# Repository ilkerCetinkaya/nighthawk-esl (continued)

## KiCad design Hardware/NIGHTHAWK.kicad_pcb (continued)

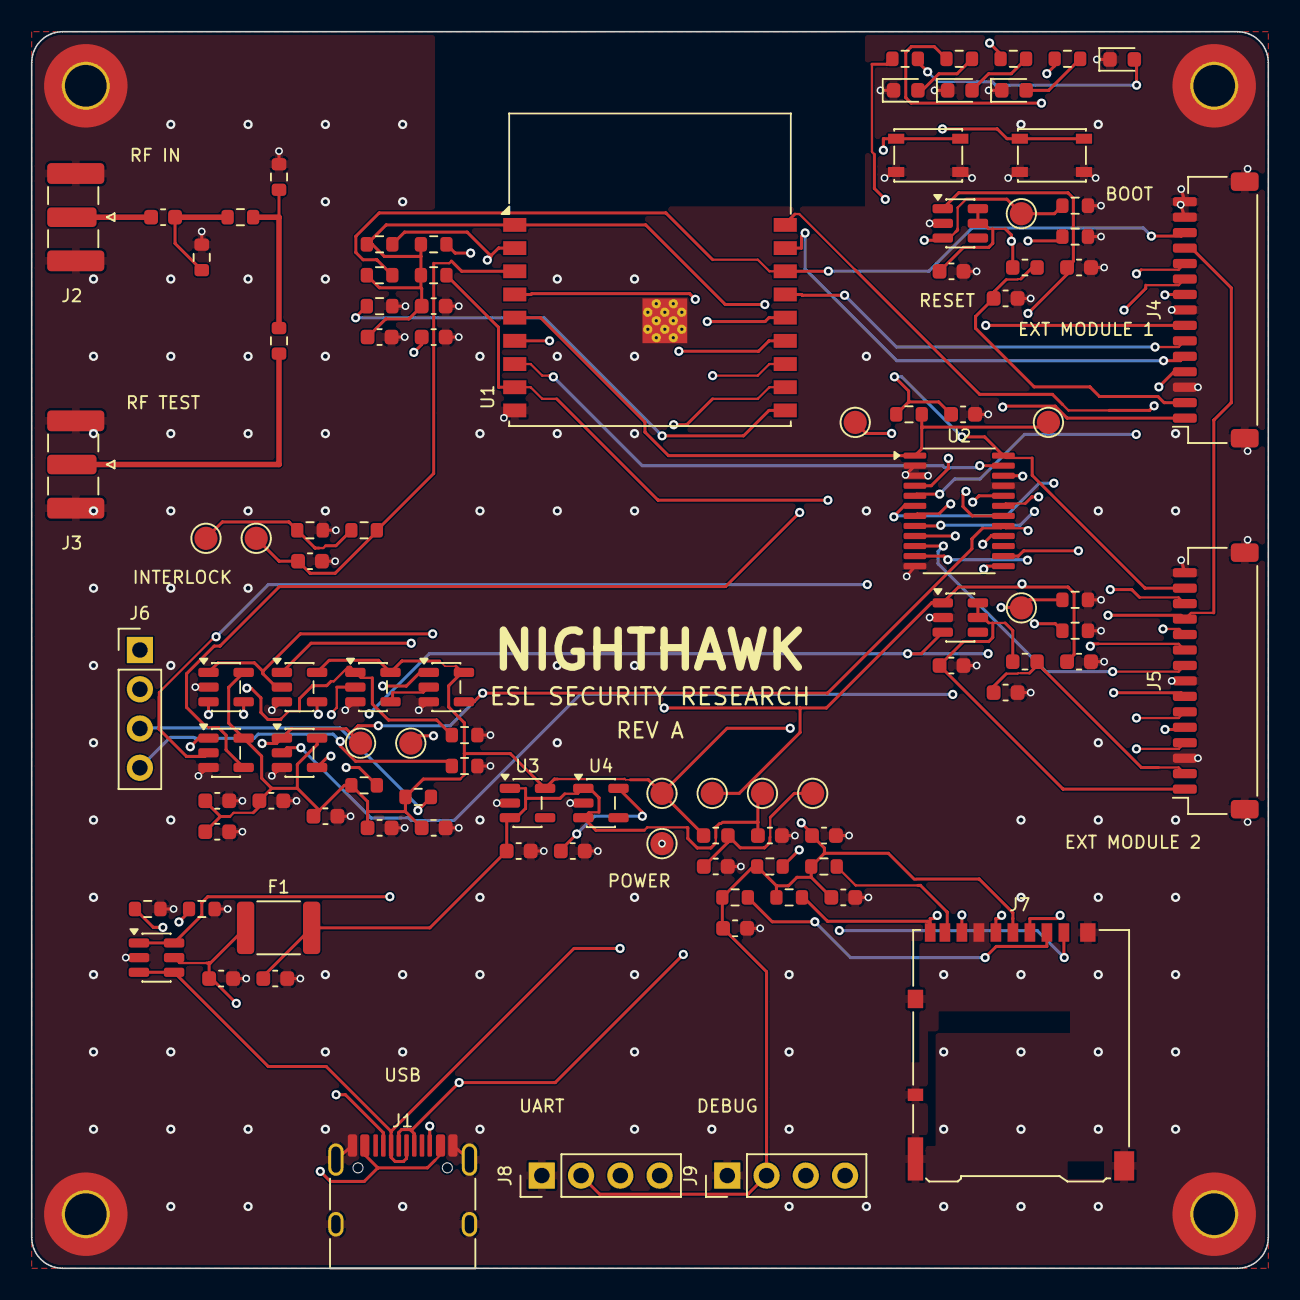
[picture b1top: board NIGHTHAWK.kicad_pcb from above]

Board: 4 copper layers, 80.0 x 80.0 mm, 106 parts (0 on the bottom side), 63 nets.

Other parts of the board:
H1, H2, H3, H4: M2.5; MountingHole_2.7mm_M2.5_Pad_TopBottom

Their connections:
GND: H1.1, H2.1, H3.1, H4.1; also elsewhere on the board

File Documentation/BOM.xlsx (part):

Reference | Quantity | Value | Description | Manufacturer | Manufacturer Part Number | LCSC Part Number | Footprint | Package | Unit Price (USD) | Total Price (USD) | Datasheet URL | Stock | Alternative | Verification Status | Assembly Status
U1 | 1 | ESP32-C3-WROOM-02-N4 | ESP32-C3 module, 4 MB flash, PCB antenna | Espressif | ESP32-C3-WROOM-02-N4 | C2934560 | RF_Module:ESP32-C3-WROOM-02 | ESP32-C3-WROOM-02 | 3.3224 | 3.3224 | https://www.lcsc.com/product-detail/C2934560.html | 13503 | C2926676 (ESP32-C3-WROOM-02U-N4, external antenna) | Verified on LCSC page (read in browser) 2026-11-07 (price at 1+ qty tier) | JLCPCB SMT
C1,C6,C7,C8,C9,C10,C11,C16,C19,C26 | 10 | 10u | 10 uF 10 V 0603 ceramic | Samsung Electro-Mechanics | CL10A106KP8NNNC | C19702 | Capacitor_SMD:C_0603_1608Metric | C_0603_1608Metric | 0.0205 | 0.205 | https://www.lcsc.com/product-detail/C19702.html | 1675120 |  | Verified on LCSC page (read in browser) 2026-11-07 (price at 20+ qty tier) | JLCPCB SMT
C2,C4,C5,C13,C20,C21,C22,C23,C24,C25,C27 | 11 | 100n | 100 nF 16 V X7R 0603 | YAGEO | CC0603KRX7R7BB104 | C108079 | Capacitor_SMD:C_0603_1608Metric | C_0603_1608Metric | 0.0121 | 0.1331 | https://www.lcsc.com/product-detail/C108079.html | 1165800 |  | Verified on LCSC page (read in browser) 2026-11-07 (price at 50+ qty tier) | JLCPCB SMT
R1,R4,R5,R6,R13,R15,R16,R17,R18,R19,R20,R23,R24,R25,R26 | 15 | 10k | 10 kohm 1% 0603 resistor | UNI-ROYAL | 0603WAF1002T5E | C25804 | Resistor_SMD:R_0603_1608Metric | R_0603_1608Metric | 0.0024 | 0.036 | https://www.lcsc.com/product-detail/C25804.html | 3592800 |  | Verified on LCSC page (read in browser) 2026-11-07 (price at 100+ qty tier) | JLCPCB SMT
C3,C14,C15,C17,C18 | 5 | 1u | 1 uF 0603 ceramic | Samsung Electro-Mechanics | CL10A105KB8NNNC | C15849 | Capacitor_SMD:C_0603_1608Metric | C_0603_1608Metric | 0.011 | 0.05499999999999999 | https://www.lcsc.com/product-detail/C15849.html | 1524300 |  | Verified on LCSC page (read in browser) 2026-11-07 (price at 50+ qty tier) | JLCPCB SMT
R2,R3 | 2 | 4.7k | 4.7 kohm 1% 0603 resistor | UNI-ROYAL | 0603WAF4701T5E | C23162 | Resistor_SMD:R_0603_1608Metric | R_0603_1608Metric | 0.0028 | 0.0056 | https://www.lcsc.com/product-detail/C23162.html | 3969400 |  | Verified on LCSC page (read in browser) 2026-11-07 (price at 100+ qty tier) | JLCPCB SMT
U2 | 1 | TCA9555PWR | 16-bit I2C GPIO expander TSSOP-24 | Texas Instruments | TCA9555PWR | C465732 | Package_SO:TSSOP-24_4.4x7.8mm_P0.65mm | TSSOP-24_4.4x7.8mm_P0.65mm | 0.7076 | 0.7076 | https://www.lcsc.com/product-detail/C465732.html | 27264 |  | Verified on LCSC page (read in browser) 2026-11-07 (price at 1+ qty tier) | JLCPCB SMT
J1 | 1 | TYPE-C-31-M-12 | USB-C receptacle 16-pin SMT | Korean Hroparts Elec | TYPE-C-31-M-12 | C165948 | Connector_USB:USB_C_Receptacle_HRO_TYPE-C-31-M-12 | USB_C_Receptacle_HRO_TYPE-C-31-M-12 | 0.1736 | 0.1736 | https://www.lcsc.com/product-detail/C165948.html | 308460 |  | Verified on LCSC page (read in browser) 2026-11-07 (price at 5+ qty tier) | JLCPCB SMT
R7,R8 | 2 | 5.1k | 5.1 kohm 1% 0603 resistor | UNI-ROYAL | 0603WAF5101T5E | C23186 | Resistor_SMD:R_0603_1608Metric | R_0603_1608Metric | 0.0016 | 0.0032 | https://www.lcsc.com/product-detail/C23186.html | 15176600 |  | Verified on LCSC page (read in browser) 2026-11-07 (price at 100+ qty tier) | JLCPCB SMT
D1 | 1 | USBLC6-2SC6 | USB ESD protection | STMicroelectronics | USBLC6-2SC6 | C7519 | Package_TO_SOT_SMD:SOT-23-6 | SOT-23-6 | 0.1639 | 0.1639 | https://www.lcsc.com/product-detail/C7519.html | 27270 |  | Verified on LCSC page (read in browser) 2026-11-07 (price at 5+ qty tier) | JLCPCB SMT
F1 | 1 | MF-MSMF050-2 | PTC resettable fuse 1812 0.5 A hold | Bourns | MF-MSMF050-2 | C17313 | Fuse:Fuse_1812_4532Metric | Fuse_1812_4532Metric | 0.0859 | 0.0859 | https://www.lcsc.com/product-detail/C17313.html | 112260 |  | Verified on LCSC page (read in browser) 2026-11-07 (price at 10+ qty tier) | JLCPCB SMT
U3,U4 | 2 | TLV75533PDBVR | 3.3 V 500 mA LDO, digital rail | Texas Instruments | TLV75533PDBVR | C404027 | Package_TO_SOT_SMD:SOT-23-5 | SOT-23-5 | 0.1227 | 0.2454 | https://www.lcsc.com/product-detail/C404027.html | 93165 |  | Verified on LCSC page (read in browser) 2026-11-07 (price at 5+ qty tier) | JLCPCB SMT
FB1,FB2,FB3 | 3 | 600R@100MHz | Ferrite bead 600 ohm 0603 | Murata | BLM18AG601SN1D | C19330 | Inductor_SMD:L_0603_1608Metric | L_0603_1608Metric | 0.0122 | 0.0366 | https://www.lcsc.com/product-detail/C19330.html | 420500 |  | Verified on LCSC page (read in browser) 2026-11-07 (price at 50+ qty tier) | JLCPCB SMT
J2 | 1 | RF IN | SMA edge-mount 50 ohm | Samtec | SMA-J-P-H-ST-EM1 | C5199907 | Connector_Coaxial:SMA_Samtec_SMA-J-P-H-ST-EM1_EdgeMount | SMA_Samtec_SMA-J-P-H-ST-EM1_EdgeMount | 5.454 | 5.454 | https://www.lcsc.com/product-detail/C5199907.html | 204 |  | Verified on LCSC page (read in browser) 2026-11-07 (price at 1+ qty tier) | JLCPCB SMT, verify edge-mount placement
J3 | 1 | RF TEST | SMA edge-mount 50 ohm | Samtec | SMA-J-P-H-ST-EM1 | C5199907 | Connector_Coaxial:SMA_Samtec_SMA-J-P-H-ST-EM1_EdgeMount | SMA_Samtec_SMA-J-P-H-ST-EM1_EdgeMount | 5.454 | 5.454 | https://www.lcsc.com/product-detail/C5199907.html | 204 |  | Verified on LCSC page (read in browser) 2026-11-07 (price at 1+ qty tier) | JLCPCB SMT, verify edge-mount placement
C12 | 1 | 100p | 100 pF 50 V C0G 0603 | Samsung Electro-Mechanics | CL10C101JB8NNNC | C14858 | Capacitor_SMD:C_0603_1608Metric | C_0603_1608Metric | 0.0083 | 0.0083 | https://www.lcsc.com/product-detail/C14858.html | 865500 |  | Verified on LCSC page (read in browser) 2026-11-07 (price at 50+ qty tier) | JLCPCB SMT
R9,R12 | 2 | 0R | 0 ohm 0603 resistor | UNI-ROYAL | 0603WAF0000T5E | C21189 | Resistor_SMD:R_0603_1608Metric | R_0603_1608Metric | 0.0022 | 0.0044 | https://www.lcsc.com/product-detail/C21189.html | 10241400 |  | Verified on LCSC page (read in browser) 2026-11-07 (price at 100+ qty tier) | JLCPCB SMT
R14,R21,R22,R27,R28,R29,R30 | 7 | 1k | 1 kohm 1% 0603 resistor | UNI-ROYAL | 0603WAF1001T5E | C21190 | Resistor_SMD:R_0603_1608Metric | R_0603_1608Metric | 0.0017 | 0.0119 | https://www.lcsc.com/product-detail/C21190.html | 2313200 |  | Verified on LCSC page (read in browser) 2026-11-07 (price at 100+ qty tier) | JLCPCB SMT
J4 | 1 | EXT MODULE 1 | Board-to-wire 15 pin 1 mm connector | JST | SM15B-SRSS-TB(LF)(SN) | C160414 | Connector_JST:JST_SH_SM15B-SRSS-TB_1x15-1MP_P1.00mm_Horizontal | JST_SH_SM15B-SRSS-TB_1x15-1MP_P1.00mm_Horizontal | 0.8045 | 0.8045 | https://www.lcsc.com/product-detail/C160414.html | 11569 |  | Verified on LCSC page (read in browser) 2026-11-07 (price at 1+ qty tier) | JLCPCB SMT
U5,U6 | 2 | TPS22918DBVR | Load switch, RF module supply gate | Texas Instruments | TPS22918DBVR | C131941 | Package_TO_SOT_SMD:SOT-23-6 | SOT-23-6 | 0.3454 | 0.6908 | https://www.lcsc.com/product-detail/C131941.html | 70550 |  | Reported from LCSC page by sub-agent, not re-read (price at 5+ qty tier) | JLCPCB SMT
J5 | 1 | EXT MODULE 2 | Board-to-wire 15 pin 1 mm connector | JST | SM15B-SRSS-TB(LF)(SN) | C160414 | Connector_JST:JST_SH_SM15B-SRSS-TB_1x15-1MP_P1.00mm_Horizontal | JST_SH_SM15B-SRSS-TB_1x15-1MP_P1.00mm_Horizontal | 0.8045 | 0.8045 | https://www.lcsc.com/product-detail/C160414.html | 11569 |  | Verified on LCSC page (read in browser) 2026-11-07 (price at 1+ qty tier) | JLCPCB SMT
U7 | 1 | TPS3823-33DBVR | Supervisor with watchdog, 2.93 V threshold | Texas Instruments | TPS3823-33DBVR | C7719 | Package_TO_SOT_SMD:SOT-23-5 | SOT-23-5 | 0.4609 | 0.4609 | https://www.lcsc.com/product-detail/C7719.html | 55321 | C20032 TPS3828-33DBVR (agent-reported, not checked) | Reported from LCSC page by sub-agent, not re-read (price at 1+ qty tier) | JLCPCB SMT
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
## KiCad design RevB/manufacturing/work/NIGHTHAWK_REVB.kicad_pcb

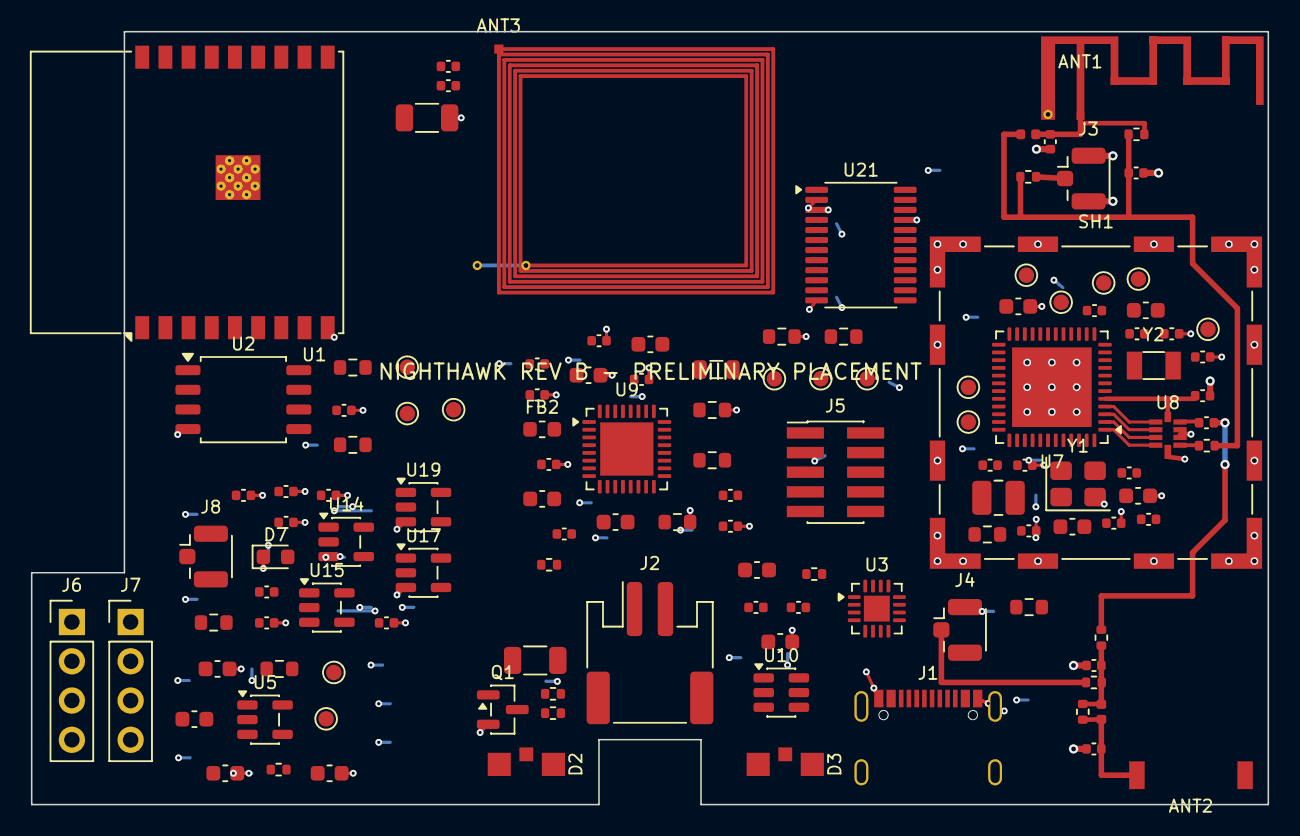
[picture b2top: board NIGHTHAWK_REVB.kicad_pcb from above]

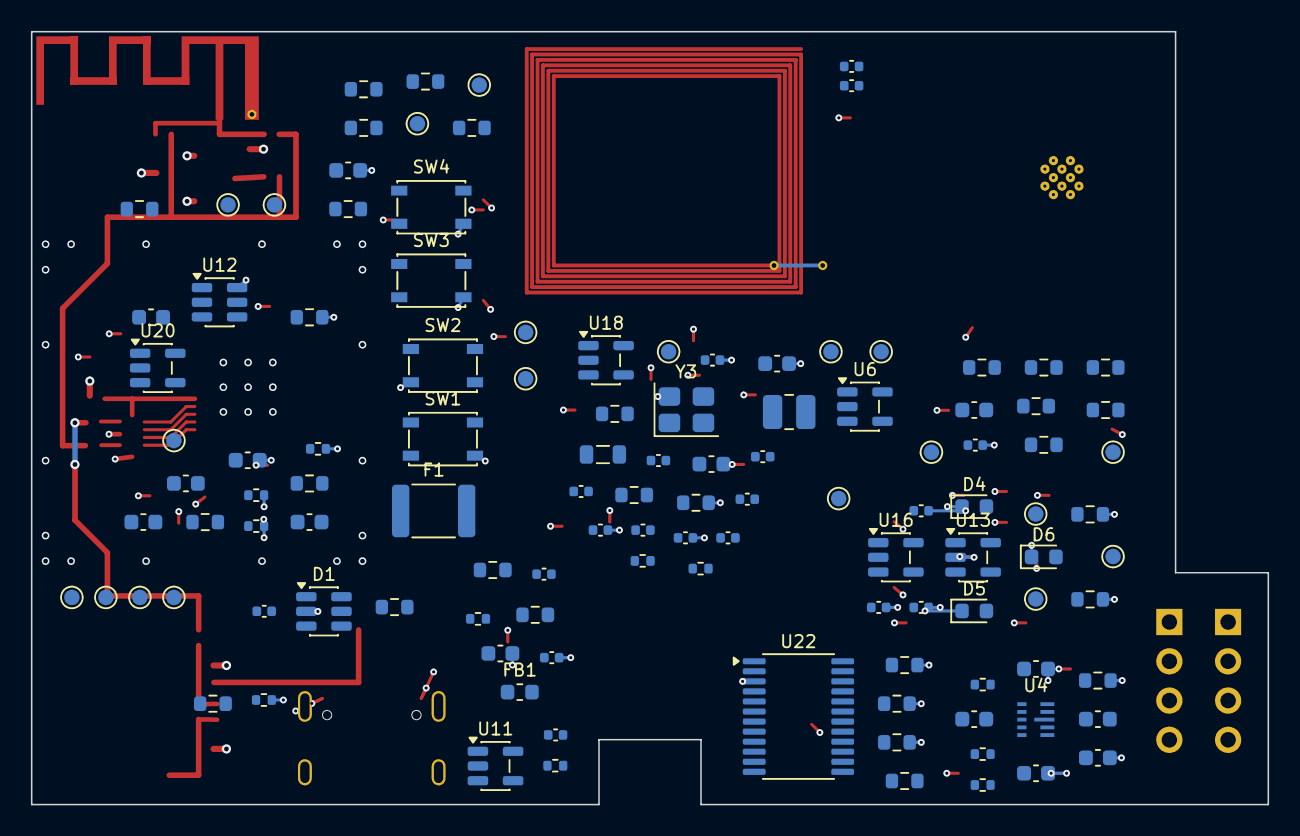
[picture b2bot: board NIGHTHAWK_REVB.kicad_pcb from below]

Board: 4 copper layers, 80.0 x 50.0 mm, 241 parts (116 on the bottom side), 129 nets.

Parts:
ANT1: 2.4GHz IFA; IFA_AN043_15.2x5.7
ANT2: 0868AT43A0020E; Johanson_0868AT43A0020
ANT3: NFC coil; NFC_COIL_18x16_6T
C1, C6, C8, C9, C10, C11, C14, C15, C16, C17, C18, C19, C24, C25, C66: 10u; C_0603_1608Metric
C2, C4, C5, C20, C21, C22, C23, C27, C28, C47, C67, C70, C72, C73, C74, C75, C76, C77, C78, C79, C80, C81, C82, C83: 100n; C_0402_1005Metric
C3, C7, C29, C65, C68, C71: 1u; C_0603_1608Metric
C12, C13, C26: 22u; C_0603_1608Metric
C30, C31, C32, C33, C62: 12p; C_0402_1005Metric
C34, C35, C59: 100p; C_0402_1005Metric
C36, C84: 1p; C_0402_1005Metric
C37: 3.9p; C_0402_1005Metric
C38: 0.3p; C_0402_1005Metric
C39, C41, C43, C45, C48: 2.2u; C_0603_1608Metric
C40, C42, C44, C46: 10n; C_0402_1005Metric
C49, C50: 15p; C_0402_1005Metric
C51, C52: 1.5n; C_0402_1005Metric
C53, C54: 1.2n; C_0402_1005Metric
C55, C58: 680p; C_0402_1005Metric
C56: 10p; C_0402_1005Metric
C57: 220p; C_0402_1005Metric
C60: 27p; C_0402_1005Metric
C61: 47p; C_0402_1005Metric
C63: 39p; C_0402_1005Metric
C64: 2.2p; C_0402_1005Metric
C69: 1.5p; C_0402_1005Metric
D1: USBLC6-2SC6; SOT-23-6
D2: VSMB10940; VSMB10940_SideView_3x2
D3: VEMD10940F; VEMD10940F_SideView_3x2
D4, D5: GREEN; LED_0603_1608Metric
D6: WHITE; LED_0603_1608Metric
D7: RED; LED_0603_1608Metric
F1: MF-MSMF050-2; Fuse_1812_4532Metric
FB1, FB2: 600R@100MHz; L_0603_1608Metric
J1: TYPE-C-31-M-12; HRO_TYPE-C-31-M-12_DS
J2: BATT; JST_PH_S2B-PH-SM4-TB_1x02-1MP_P2.00mm_Horizontal
J3, J4: U.FL; U.FL_Hirose_U.FL-R-SMT-1_Vertical
J5: CC1352R JTAG; PinHeader_2x05_P1.27mm_Vertical_SMD
J6: INTERLOCK; PinHeader_1x04_P2.54mm_Vertical
J7: DEBUG; PinHeader_1x04_P2.54mm_Vertical
J8: U.FL NFC; U.FL_Hirose_U.FL-R-SMT-1_Vertical
L1: 0.47u; L_1008_2520Metric
L2: 10u; L_1008_2520Metric
L3: 1n; L_0402_1005Metric
L4: 18n; L_0402_1005Metric
L5: 150n; L_0805_2012Metric
L6: 330n; L_0805_2012Metric
Q1: AO3400A; SOT-23
R1, R2, R3, R6, R7, R8, R9, R10, R13, R18, R19, R33, R34, R35, R36, R37, R38, R46, R48, R50, R52, R53, R54, R55, R56, R57, R64: 10k; R_0603_1608Metric
R4, R5: 4.7k; R_0603_1608Metric
R11, R12: 5.1k; R_0603_1608Metric
R14: 3.09k; R_0402_1005Metric
R15: 1.78k; R_0402_1005Metric
R16: 68k; R_0402_1005Metric
R17: 2.94k; R_0402_1005Metric
R20, R23, R45, R51: 100k; R_0402_1005Metric
R21: 562k; R_0402_1005Metric
R22: 91k; R_0402_1005Metric
R24, R25: 0R; R_0603_1608Metric
R26, R27, R28, R29, R30, R31, R39, R40, R41: 0R; R_0402_1005Metric
R32, R58, R59, R60, R61, R62, R63: 1k; R_0603_1608Metric
R42: 845; R_1206_3216Metric
R43: 20; R_1206_3216Metric
R44: 22; R_0402_1005Metric
R47: 100; R_0402_1005Metric
R49: 6.8k; R_0402_1005Metric
SH1: 36103205S; Wuerth_36103205_20x20mm
SW1: RESET; SW_SPST_PTS810
SW2: BOOT; SW_SPST_PTS810
SW3: BTN1; SW_SPST_PTS810
SW4: BTN2; SW_SPST_PTS810
TP1: TP_SPI_SCK; TestPoint_Pad_D1.0mm
TP2: TP_SPI_MOSI; TestPoint_Pad_D1.0mm
TP3: TP_SPI_MISO; TestPoint_Pad_D1.0mm
TP4: TP_I2C_SDA; TestPoint_Pad_D1.0mm
TP5: TP_I2C_SCL; TestPoint_Pad_D1.0mm
TP6: TP_VBUS_F; TestPoint_Pad_D1.0mm
TP7: TP_VBAT; TestPoint_Pad_D1.0mm
TP8: TP_SYS; TestPoint_Pad_D1.0mm
TP9: TP_3V6; TestPoint_Pad_D1.0mm
TP10: TP_3V3; TestPoint_Pad_D1.0mm
TP11: TP_3V3_RF; TestPoint_Pad_D1.0mm
TP12: TP_3V3_A; TestPoint_Pad_D1.0mm
TP13: TP_BB_PG; TestPoint_Pad_D1.0mm
TP14: TP_GND; TestPoint_Pad_D1.0mm
TP15: TP_CC_UART_TX; TestPoint_Pad_D1.0mm
TP16: TP_CC_UART_RX; TestPoint_Pad_D1.0mm
TP17: TP_CC_IRQ; TestPoint_Pad_D1.0mm
TP18: TP_CC_RESET_N; TestPoint_Pad_D1.0mm
TP19: TP_IR_MOD; TestPoint_Pad_D1.0mm
TP20: TP_IR_RX; TestPoint_Pad_D1.0mm
TP21: TP_VDDR; TestPoint_Pad_D1.0mm
TP22: TP_NFC_IRQ; TestPoint_Pad_D1.0mm
TP23: TP_NFC_EN_G; TestPoint_Pad_D1.0mm
TP24: TP_NFC_TXOUT; TestPoint_Pad_D1.0mm
TP25: TP_NFC_ANT; TestPoint_Pad_D1.0mm
TP26: TP_NFC_RX1; TestPoint_Pad_D1.0mm
TP27: TP_NFC_RX2; TestPoint_Pad_D1.0mm
TP28: TP_NFC_VDDX; TestPoint_Pad_D1.0mm
TP29: TP_TIA_OUT; TestPoint_Pad_D1.0mm
TP30: TP_CMP_IN; TestPoint_Pad_D1.0mm
TP31: TP_IR_LED_K; TestPoint_Pad_D1.0mm
TP32: TP_IR_GATE; TestPoint_Pad_D1.0mm
TP33: TP_VREF; TestPoint_Pad_D1.0mm
TP34: TP_INTERLOCK_OK; TestPoint_Pad_D1.0mm
TP35: TP_ARM; TestPoint_Pad_D1.0mm
U1: ESP32-C3-WROOM-02-N4; ESP32-C3-WROOM-02
U2: GD25Q32ESIGR; SOIC-8_5.3x5.3mm_P1.27mm
U3: BQ24074RGTR; VQFN-16-1EP_3x3mm_P0.5mm_EP1.68x1.68mm
U4: TPS63802DLAR; TPS63802DLA_VSON-10_3x2mm
U5, U6: TLV75533PDBVR; SOT-23-5
U7: CC1352R1F3RGZR; Texas_RGZ0048A_VQFN-48-1EP_7x7mm_P0.5mm_EP5.15x5.15mm
U8: 0900PC15A0036001E; Johanson_0900PC15A0036_2.0x1.25mm
U9: TRF7970ARHBR; Texas_RHB0032E_VQFN-32-1EP_5x5mm_P0.5mm_EP3.45x3.45mm
U10: TPS22918DBVR; SOT-23-6
U11: OPA356AIDBVR; SOT-23-5
U12: TLV3501AIDBVR; SOT-23-6
U13: TPS3823-33DBVR; SOT-23-5
U14, U15, U16, U17, U18, U19, U20: SN74LVC1G08DBVR; SOT-23-5
U21, U22: TCA9555PWR; TSSOP-24_4.4x7.8mm_P0.65mm
Y1: 48MHz; Crystal_SMD_3225-4Pin_3.2x2.5mm
Y2: 32.768kHz; Crystal_SMD_3215-2Pin_3.2x1.5mm
Y3: 27.12MHz; Crystal_SMD_3225-4Pin_3.2x2.5mm

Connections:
3V3: C1.1, C2.1, C4.1, C15.1, C47.1, C65.1, C74.1, C75.1, C76.1, C77.1, C78.1, C79.1, C80.1, C81.1, C82.1, C83.1, J7.2, R1.1, R2.1, R3.1, R4.1, R5.1, R6.1, R7.1, R8.1, R9.1, R10.1, R18.1, R19.1, R33.1, R34.1, R58.1, R59.1, R60.1, TP10.1, U1.1, U2.8, U5.5, U9.16, U10.1, U13.5, U14.5, U15.5, U16.5, U17.5, U18.5, U19.5, U20.5, U21.24, U22.21, U22.24
3V3_A: C18.1, C70.1, C73.1, FB1.2, R47.1, R49.1, TP12.1, U11.5, U12.4
3V3_RF: C17.1, C20.1, C21.1, C22.1, C23.1, C24.1, C25.1, FB1.1, J5.1, TP11.1, U6.5, U7.13, U7.22, U7.34, U7.44
3V6: C12.1, C13.1, C14.1, C16.1, FB2.1, R21.1, R23.1, R24.1, TP9.1, U4.6, U5.1, U5.3, U6.1, U6.3
3V6_NFC: C19.1, C39.1, C40.1, FB2.2, U9.2
ANT24_A: ANT1.1, C84.1, L3.2, R28.2
ANT24_FEED: C36.1, L3.1, R26.2, R27.1, R28.1
ANT24_IPC: R26.1, U8.1
ANTSUB_A: ANT2.1, C38.1, L4.2, R31.2
ANTSUB_DC: C35.2, R29.1
ANTSUB_FEED: C37.1, L4.1, R29.2, R30.1, R31.1
ANTSUB_IPC: C35.1, U8.4
ARM: R54.1, TP35.1, U14.1, U21.9
ARM_WDG: U14.4, U16.1
BB_EN: R20.2, U4.1
BB_FB: R21.2, R22.1, U4.4
BB_L1: L1.1, U4.9
BB_L2: L1.2, U4.7
BB_MODE: R24.2, R25.1, U4.2
BB_PG: R23.2, TP13.1, U4.5
BOOT: J7.4, R3.2, SW2.1, U1.8
BQ_ILIM: R14.1, U3.12
BQ_ISET: R15.1, U3.16
BQ_ITERM: R17.1, U3.15
BQ_TMR: R16.1, U3.14
BQ_TS: R13.1, U3.1
BTN1: SW3.1, U21.15
BTN2: SW4.1, U21.16
CC1: J1.A5, R11.1
CC2: J1.B5, R12.1
CC_BSL: U7.21, U21.5
CC_IRQ: TP17.1, U7.14, U21.6
CC_RESET_G: R32.1, U17.4
CC_RESET_N: J5.10, R32.2, TP18.1, U7.35
CC_RF_BUSY: U7.11, U22.7
CC_RUN: R55.1, U17.2, U21.4
CC_TCKC: J5.4, U7.25
CC_TDI: J5.8, U7.27
CC_TDO: J5.6, U7.26
CC_TMSC: J5.2, U7.24
CC_UART_RX: TP16.1, U1.12, U7.8
CC_UART_TX: TP15.1, U1.11, U7.9
CHG_N: R19.2, U3.9, U21.17
CMP_IN: C72.2, R51.1, TP30.1, U12.3
DCDC_SW: L2.1, U7.33
DCOUPL: C29.1, U7.23
EN: C3.1, J7.3, R1.2, U1.2, U13.1, U14.2, U21.20
ENCL_OK: J6.4, R53.1, U15.2, U22.5
ESP_RF_QUIET: R64.1, U7.12, U22.6
EXP_INT: R6.2, U1.10, U21.1, U22.1
FLASH_CS: R7.2, U1.4, U2.1
FLASH_HOLD: R9.2, U2.7
FLASH_WP: R8.2, U2.3
GND: ANT1.2, ANT3.2, C1.2, C2.2, C3.2, C4.2, C5.2, C6.2, C7.2, C8.2, C9.2, C10.2, C11.2, C12.2, C13.2, C14.2, C15.2, C16.2, C17.2, C18.2, C19.2, C20.2, C21.2, C22.2, C23.2, C24.2, C25.2, C26.2, C27.2, C28.2, C29.2, C30.2, C31.2, C32.2, C33.2, C34.2, C36.2, C37.2, C38.2, C39.2, C40.2, C41.2, C42.2, C43.2, C44.2, C45.2, C46.2, C47.2, C48.2, C49.2, C50.2, C54.2, C55.2, C58.2, C59.2, C60.2, C63.2, C64.2, C65.2, C66.2, C67.2, C68.2, C70.2, C71.2, C73.2, C74.2, C75.2, C76.2, C77.2, C78.2, C79.2, C80.2, C81.2, C82.2, C83.2, C84.2, D1.2, D4.1, D5.1, D6.1, D7.1, J1.A1, J1.A12, J1.B1, J1.B12, J1.SH, J2.2, J3.2, J4.2, J5.3, J5.5, J5.9, J7.1, J8.2, Q1.2, R11.2, R12.2, R13.2, R14.2, R15.2, R16.2, R17.2, R22.2, R25.2, R35.2, R36.2, R37.2, R38.2, R42.2, R45.2, R46.2, R50.2, R52.2, R53.2, R54.2, R55.2, R56.2, R57.2, R64.2, SH1.1, SW1.2, SW2.2, SW3.2, SW4.2, TP14.1, U1.9, U1.19, U2.4, U3.4, U3.6, U3.8, U3.17, U4.3, U4.8, U5.2, U6.2, U7.49, U8.2, U8.3, U8.10, U9.6, U9.7, U9.10, U9.15, U9.29, U9.33, U10.2, U11.2, U12.2, U12.6, U13.2, U14.3, U15.3, U16.3, U17.3, U18.3, U19.3, U20.3, U21.2, U21.3, U21.12, U21.21, U22.2, U22.3, U22.12, Y1.2, Y1.4, Y3.2, Y3.4
I2C_SCL: R5.2, TP5.1, U1.7, U21.22, U22.22
I2C_SDA: R4.2, TP4.1, U1.6, U21.23, U22.23
ILK_SRC1: J6.1, R58.2
ILK_SRC2: J6.3, R59.2
INTERLOCK_OK: R61.1, TP34.1, U16.4, U17.1, U18.1, U19.1, U20.1, U21.19
IR_EN: R57.1, U19.2, U21.8
IR_GATE: Q1.1, R44.2, R45.1, TP32.1
IR_GATE_DRV: R44.1, U20.4
IR_LED_A: D2.2, R43.2
IR_LED_K: D2.1, Q1.3, TP31.1
IR_MOD: TP19.1, U7.10, U20.2
IR_PWR_ON: R46.1, U10.3, U19.4
IR_RX: TP20.1, U7.15, U12.5
IR_VCC: C66.1, C67.1, R43.1, U10.6
LEDA_3V3: D4.2, R60.2
LEDA_INTERLOCK_OK: D5.2, R61.2
LEDA_LED_FAULT: D7.2, R63.2
LEDA_LED_STATUS: D6.2, R62.2
LED_FAULT: R63.1, U21.14
LED_STATUS: R62.1, U21.13
LOOPS_OK: U15.4, U16.2
LOOP_OK: J6.2, R52.1, U15.1, U22.4
NFC_ANT: C61.1, C62.1, J8.1, R39.2, TP25.1
NFC_ASKOOK: R37.1, U9.12
NFC_BG: C48.1, U9.11
NFC_COIL_A: ANT3.1, C61.2, C62.2, C63.1, C64.1, R42.1
NFC_CS: R10.2, U1.5, U9.21
NFC_EN: R56.1, U18.2, U21.7
NFC_EN2: R36.1, U9.25
NFC_EN_G: R38.1, TP23.1, U9.28, U18.4
NFC_IO0: R35.1, U9.17
NFC_IO1: R34.2, U9.18
NFC_IO2: R33.2, U9.19
NFC_IRQ: TP22.1, U1.15, U9.13
NFC_N1: C53.1, C55.1, C56.1, L5.2, L6.1
NFC_N2: C56.2, C57.1, C59.1, C60.1, L6.2, R39.1
NFC_OSC_IN: C49.1, U9.31, Y3.1
NFC_OSC_OUT: C50.1, U9.30, Y3.3
NFC_RX1: R40.2, TP26.1, U9.8
NFC_RX2: R41.2, TP27.1, U9.9
NFC_RXM1: C53.2, C54.1, R40.1
NFC_RXM2: C57.2, C58.1, R41.1
NFC_T1: C51.2, C52.2, L5.1
NFC_TXOUT: C51.1, C52.1, TP24.1, U9.5
NFC_VDDA: C41.1, C42.1, U9.1
NFC_VDDRF: C43.1, C44.1, U9.3, U9.4
NFC_VDDX: C45.1, C46.1, TP28.1, U9.32
PD_BIAS: C68.1, D3.1, R47.2
PGOOD_N: R18.2, U3.7, U21.18
RESET_BTN: SW1.1, U13.3
RF24_N: U7.2, U8.8
RF24_P: U7.1, U8.9
RFSUB_N: U7.4, U8.6
RFSUB_P: U7.3, U8.7
RX_TX: C34.1, U7.5, U8.5
SPI_MISO: TP3.1, U1.17, U2.2, U9.23
SPI_MOSI: TP2.1, U1.3, U2.5, U9.24
SPI_SCK: TP1.1, U1.18, U2.6, U9.26
SYS: C8.1, C10.1, C11.1, R20.1, TP8.1, U3.5, U3.10, U3.11, U4.10
TIA_IN: C69.1, D3.2, R48.1, U11.4
TIA_OUT: C69.2, C72.1, R48.2, TP29.1, U11.1
UFL24_C: J3.1, R27.2
UFLSUB_C: J4.1, R30.2
USB_DN: D1.3, D1.4, J1.A7, J1.B7, U1.13
USB_DP: D1.1, D1.6, J1.A6, J1.B6, U1.14
VBAT: C9.1, J2.1, TP7.1, U3.2, U3.3
VBUS: C5.1, D1.5, F1.1, J1.A4, J1.A9, J1.B4, J1.B9
VBUS_F: C6.1, C7.1, F1.2, TP6.1, U3.13
VDDR: C26.1, C27.1, C28.1, L2.2, TP21.1, U7.45, U7.48
VREF: C71.1, R49.2, R50.1, R51.2, TP33.1, U11.3, U12.1
WDI: R2.2, U1.16, U13.4
X32K_Q1: C32.1, U7.6, Y2.1
X32K_Q2: C33.1, U7.7, Y2.2
X48M_N: C30.1, U7.46, Y1.1
X48M_P: C31.1, U7.47, Y1.3

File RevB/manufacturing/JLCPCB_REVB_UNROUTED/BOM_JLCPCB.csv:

Comment,Designator,Footprint,LCSC Part Number
10u,"C1,C6,C8,C9,C10,C11,C14,C15,C16,C17,C18,C19,C24,C25,C66",C_0603_1608Metric,C19702
100n,"C2,C4,C5,C20,C21,C22,C23,C27,C28,C47,C67,C70,C72,C73,C74,C75,C76,C77,C78,C79,C80,C81,C82,C83",C_0402_1005Metric,C1525
1u,"C3,C7,C29,C65,C68,C71",C_0603_1608Metric,C15849
22u,"C12,C13,C26",C_0603_1608Metric,C59461
100p,"C34,C35,C59",C_0402_1005Metric,C77177
2.2u,"C39,C41,C43,C45,C48",C_0603_1608Metric,C23630
10n,"C40,C42,C44,C46",C_0402_1005Metric,C15195
15p,"C49,C50",C_0402_1005Metric,C86285
1.5n,"C51,C52",C_0402_1005Metric,C668348
1.2n,"C53,C54",C_0402_1005Metric,C3010430
680p,"C55,C58",C_0402_1005Metric,C307451
10p,C56,C_0402_1005Metric,C32949
220p,C57,C_0402_1005Metric,C307445
27p,C60,C_0402_1005Metric,C86287
47p,C61,C_0402_1005Metric,C1567
12p,C62,C_0402_1005Metric,C1547
39p,C63,C_0402_1005Metric,C86288
1.5p,C69,C_0402_1005Metric,C76957
USBLC6-2SC6,D1,SOT-23-6,C7519
VSMB10940,D2,VSMB10940_SideView_3x2,C4749241
VEMD10940F,D3,VEMD10940F_SideView_3x2,C3211032
GREEN,"D4,D5",LED_0603_1608Metric,C51933293
WHITE,D6,LED_0603_1608Metric,C51933297
RED,D7,LED_0603_1608Metric,C2286
MF-MSMF050-2,F1,Fuse_1812_4532Metric,C17313
600R@100MHz,"FB1,FB2",L_0603_1608Metric,C19330
TYPE-C-31-M-12,J1,HRO_TYPE-C-31-M-12_DS,C165948
BATT,J2,JST_PH_S2B-PH-SM4-TB_1x02-1MP_P2.00mm_Horizontal,C295747
INTERLOCK,J6,PinHeader_1x04_P2.54mm_Vertical,C2691448
DEBUG,J7,PinHeader_1x04_P2.54mm_Vertical,C2691448
0.47u,L1,L_1008_2520Metric,C703140
10u,L2,L_1008_2520Metric,C703141
150n,L5,L_0805_2012Metric,C76739
330n,L6,L_0805_2012Metric,C87521
AO3400A,Q1,SOT-23,C20917
10k,"R1,R2,R3,R6,R7,R8,R9,R10,R13,R18,R19,R33,R34,R35,R36,R37,R38,R46,R48,R50,R52,R53,R54,R55,R56,R57,R64",R_0603_1608Metric,C25804
4.7k,"R4,R5",R_0603_1608Metric,C23162
5.1k,"R11,R12",R_0603_1608Metric,C23186
3.09k,R14,R_0402_1005Metric,C11460
1.78k,R15,R_0402_1005Metric,C113478
68k,R16,R_0402_1005Metric,C36871
2.94k,R17,R_0402_1005Metric,C25886
100k,"R20,R23,R45,R51",R_0402_1005Metric,C25741
562k,R21,R_0402_1005Metric,C48838
91k,R22,R_0402_1005Metric,C4147
0R,R24,R_0603_1608Metric,C21189
0R,"R26,R28,R29,R39,R40,R41",R_0402_1005Metric,C17168
1k,"R32,R58,R59,R60,R61,R62,R63",R_0603_1608Metric,C21190
845,R42,R_1206_3216Metric,C247179
20,R43,R_1206_3216Metric,C17955
22,R44,R_0402_1005Metric,C114765
100,R47,R_0402_1005Metric,C25076
6.8k,R49,R_0402_1005Metric,C25917
RESET,SW1,SW_SPST_PTS810,C221895
BOOT,SW2,SW_SPST_PTS810,C221895
BTN1,SW3,SW_SPST_PTS810,C221895
BTN2,SW4,SW_SPST_PTS810,C221895
ESP32-C3-WROOM-02-N4,U1,ESP32-C3-WROOM-02,C2934560
GD25Q32ESIGR,U2,SOIC-8_5.3x5.3mm_P1.27mm,C2832998
BQ24074RGTR,U3,VQFN-16-1EP_3x3mm_P0.5mm_EP1.68x1.68mm,C54313
TPS63802DLAR,U4,TPS63802DLA_VSON-10_3x2mm,C2845237
TLV75533PDBVR,"U5,U6",SOT-23-5,C404027
CC1352R1F3RGZR,U7,Texas_RGZ0048A_VQFN-48-1EP_7x7mm_P0.5mm_EP5.15x5.15mm,C2151581
TRF7970ARHBR,U9,Texas_RHB0032E_VQFN-32-1EP_5x5mm_P0.5mm_EP3.45x3.45mm,C117004
TPS22918DBVR,U10,SOT-23-6,C131941
OPA356AIDBVR,U11,SOT-23-5,C183100
TPS3823-33DBVR,U13,SOT-23-5,C7719
SN74LVC1G08DBVR,"U14,U15,U16,U17,U18,U19,U20",SOT-23-5,C7666
TCA9555PWR,"U21,U22",TSSOP-24_4.4x7.8mm_P0.65mm,C465732
48MHz,Y1,Crystal_SMD_3225-4Pin_3.2x2.5mm,C2925606
32.768kHz,Y2,Crystal_SMD_3215-2Pin_3.2x1.5mm,C48615
27.12MHz,Y3,Crystal_SMD_3225-4Pin_3.2x2.5mm,C29975

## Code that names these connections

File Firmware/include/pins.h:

#pragma once

#define PIN_SPI_SCK 0
#define PIN_SPI_MOSI 1
#define PIN_I2C_SCL 2
#define PIN_SPI_MISO 3
#define PIN_RSSI_ADC 4
#define PIN_SD_CS 5
#define PIN_EXP_INT 6
#define PIN_WDI 7
#define PIN_I2C_SDA 8
#define PIN_BOOT 9
#define PIN_ARM 10
#define PIN_USB_DN 18
#define PIN_USB_DP 19
#define PIN_UART_RX 20
#define PIN_UART_TX 21

#define ADC_CH_RSSI 4

#define EXP_I2C_ADDR 0x20

#define EXP_RF1_CS 0
#define EXP_RF1_IRQ 1
#define EXP_RF1_RST 2
#define EXP_RF1_EN 3
#define EXP_RF1_IO1 4
#define EXP_RF2_CS 5
#define EXP_RF2_IRQ 6
#define EXP_RF2_RST 7
#define EXP_RF2_EN 8
#define EXP_RF2_IO1 9
#define EXP_SPARE2 10
#define EXP_SD_CD 11
#define EXP_INTERLOCK_OK 12
#define EXP_LED_STATUS 13
#define EXP_LED_FAULT 14
#define EXP_SPARE 15

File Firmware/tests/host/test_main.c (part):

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static fw_t fw;
static uint32_t now;

static bool arm_pin(void) { return !hw.mcu_in_reset && hw.arm_driven; }
static bool en_pin(void) { return !hw.mcu_in_reset; }
static bool interlock_ok(void) { return arm_pin() && en_pin() && hw.loop_ok && hw.encl_ok; }
static bool rail(int i) { return interlock_ok() && (hw.tca_out & (i == 1 ? EN1 : EN2)); }

static void fw_boot(void)
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    return 0xFFFFFFFFu;
}

static bool cond_arm_low(void) { return !arm_pin(); }
static bool cond_rails_off(void) { return !rail(1) && !rail(2); }
static bool cond_reset(void) { return hw.mcu_in_reset; }
static bool cond_booted(void) { return !hw.mcu_in_reset && fw.booted; }
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        printf("  ttout=%u ms: ARM low %u ms after stall, hardware reset %u ms after that\n", tt[k], t_arm, t_rst);
        first_time(cond_booted, 1000);
        step(300);
        CHECK(fw.sup.state == SUP_DISARMED && !arm_pin(), "after reset: DISARMED, ARM low");
        CHECK(!rail(1) && !rail(2), "after reset rails off");
        step(2000);
        CHECK(!rail(1) && !rail(2), "rails stay off until explicit arm");
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            printf("  WDI stuck %s, ttout=%u ms: rails on for %u ms after supervisor stall\n", level ? "high (idle)" : "low (stalled mid-pulse)", tt[k], t_rail);
            first_time(cond_booted, 1000);
            step(300);
            CHECK(!arm_pin() && fw.sup.state == SUP_DISARMED, "after watchdog reset: ARM low, DISARMED");
        }
    }
    printf("  exposure is bounded by the TPS3823 time-out (0.9 / 1.6 / 2.5 s min/typ/max); it is not zero\n");
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    CHECK(hw.resets == (int)resets, "no watchdog reset: system alive and safe");
    fw.arm_req = true;
    step(500);
    CHECK(fw.sup.state == SUP_FAULT && !arm_pin(), "arm refused while latched");
    fw.disarm_req = true;
    step(500);
    CHECK(fw.sup.state == SUP_FAULT, "disarm cannot clear fault while I2C is down");
    CHECK(!arm_pin() && !rail(1) && !rail(2), "still safe");
    fw.i2c_fail = false;
    step(500);
    CHECK(fw.sup.state == SUP_DISARMED, "disarm completes after I2C returns, state %s", sup_state_name(fw.sup.state));
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    bool arm_ever_high = false;
    for (int i = 0; i < 1500; i++) {
        step(1);
        arm_ever_high = arm_ever_high || arm_pin();
    }
    CHECK(!arm_ever_high, "ARM must never rise while enables cannot be cleared");
    CHECK(fw.sup.state == SUP_DISARMED && fw.sup.reason == SUP_REASON_ARM_ABORTED, "arming aborted, got %s/%s", sup_state_name(fw.sup.state), sup_reason_name(fw.sup.reason));
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    CHECK(hw.resets == resets, "task alive: no watchdog reset (execution progress is healthy, peripheral is not)");
    fw.arm_req = true;
    step(300);
    CHECK(fw.sup.state == SUP_FAULT && !arm_pin(), "arm refused while peripheral unhealthy");
    fw.i2c_fail = false;
    fw.disarm_req = true;
    step(150);
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    step(150);
    fw.arm_req = true;
    step(500);
    CHECK(fw.sup.state == SUP_DISARMED && !arm_pin(), "arm refused when an enable PIN reads high although output register is low");
    printf("  enable pin read high with output low: arm refused\n");
}

static sup_in_t mk_in(uint32_t seq, uint32_t time_ms, bool valid, bool enables_low)
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    bool arm_high = false;
    for (int i = 0; i < 1500; i++) {
        step(1);
        arm_high = arm_high || arm_pin();
    }
    CHECK(!arm_high && fw.sup.state == SUP_DISARMED, "enable pin HIGH during PRECHECK: ARM never rose");
    reset_world(1600);
    step(500);
    fw.output_mismatch = true;
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    arm_high = false;
    for (int i = 0; i < 1500; i++) {
        step(1);
        arm_high = arm_high || arm_pin();
    }
    CHECK(!arm_high && fw.sup.state == SUP_DISARMED, "output register mismatch during PRECHECK: ARM never rose");
    reset_world(1600);
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    fw.arm_req = true;
    step(1500);
    CHECK(fw.sup.state == SUP_OPEN && !rail(1) && !rail(2), "REV A: loops are not observable before ARM; ARM rises, the first ARMING sample finds INTERLOCK_OK low -> OPEN, rails stay off (state %s)", sup_state_name(fw.sup.state));
    printf("  pin high / mismatch abort before ARM; REV A open loop is detected in ARMING (rails off throughout)\n");
}

static void test_integrated_stale(void)
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    bool arm_high = false;
    for (int i = 0; i < 2500; i++) {
        step(1);
        arm_high = arm_high || arm_pin();
    }
    CHECK(!arm_high, "ARM must never rise with a stalled sampler");
    printf("  stalled sampler: ARM never rose (state %s)\n", sup_state_name(fw.sup.state));
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        }
        CHECK(!rail(1) && !rail(2), "rails off immediately (combinational hardware)");
        step(150);
        CHECK(fw.sup.state == SUP_OPEN && !arm_pin(), "supervisor latches OPEN and drives ARM low, state %s", sup_state_name(fw.sup.state));
        hw.loop_ok = true;
        hw.encl_ok = true;
        step(500);
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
